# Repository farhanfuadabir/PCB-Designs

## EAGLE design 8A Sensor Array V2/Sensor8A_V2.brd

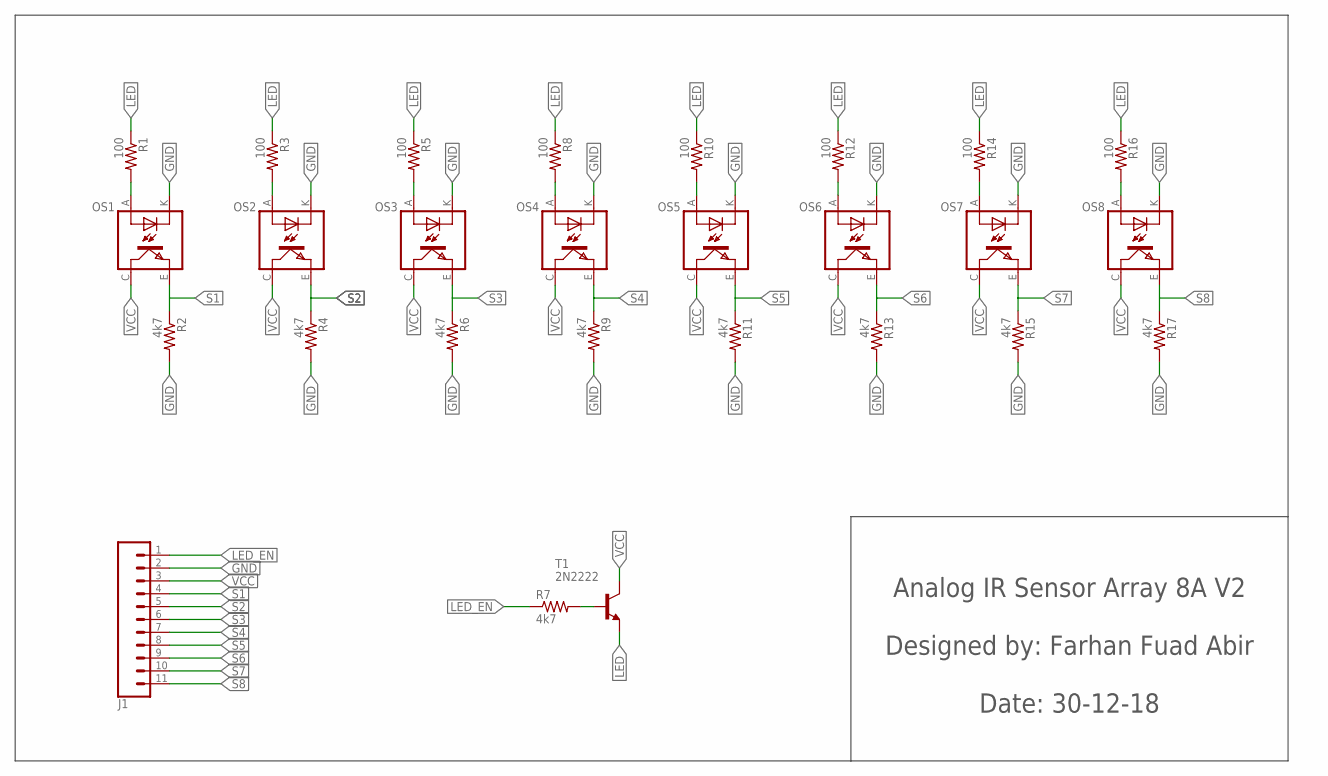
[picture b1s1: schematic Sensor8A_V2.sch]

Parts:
J1: CONN_11LONGPADS; 1X11_LONGPADS
OS1, OS2, OS3, OS4, OS5, OS6, OS7, OS8: TCRT5000
R1, R3, R5, R8, R10, R12, R14, R16: 100; 0204/7
R2, R4, R6, R7, R9, R11, R13, R15, R17: 4k7; 0204/7
T1: 2N2222; TO92-EBC-OVAL

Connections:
GND: J1.2, OS1.K (CATHODE), OS2.K (CATHODE), OS3.K (CATHODE), OS4.K (CATHODE), OS5.K (CATHODE), OS6.K (CATHODE), OS7.K (CATHODE), OS8.K (CATHODE), R2.2, R4.2, R6.2, R9.2, R11.2, R13.2, R15.2, R17.2
LED: R1.1, R3.1, R5.1, R8.1, R10.1, R12.1, R14.1, R16.1, T1.E
LED_EN: J1.1, R7.1
unnamed: OS1.A (ANODE), R1.2
unnamed: OS2.A (ANODE), R3.2
unnamed: OS3.A (ANODE), R5.2
unnamed: OS4.A (ANODE), R8.2
unnamed: OS5.A (ANODE), R10.2
unnamed: OS6.A (ANODE), R12.2
unnamed: OS7.A (ANODE), R14.2
unnamed: OS8.A (ANODE), R16.2
unnamed: R7.2, T1.B
S1: J1.4, OS1.E (EMITTER), R2.1
S2: J1.5, OS2.E (EMITTER), R4.1
S3: J1.6, OS3.E (EMITTER), R6.1
S4: J1.7, OS4.E (EMITTER), R9.1
S5: J1.8, OS5.E (EMITTER), R11.1
S6: J1.9, OS6.E (EMITTER), R13.1
S7: J1.10, OS7.E (EMITTER), R15.1
S8: J1.11, OS8.E (EMITTER), R17.1
VCC: J1.3, OS1.C (COLLECTOR), OS2.C (COLLECTOR), OS3.C (COLLECTOR), OS4.C (COLLECTOR), OS5.C (COLLECTOR), OS6.C (COLLECTOR), OS7.C (COLLECTOR), OS8.C (COLLECTOR), T1.C

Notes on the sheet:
Analog IR Sensor Array 8A V2 Designed by: Farhan Fuad Abir Date: 30-12-18

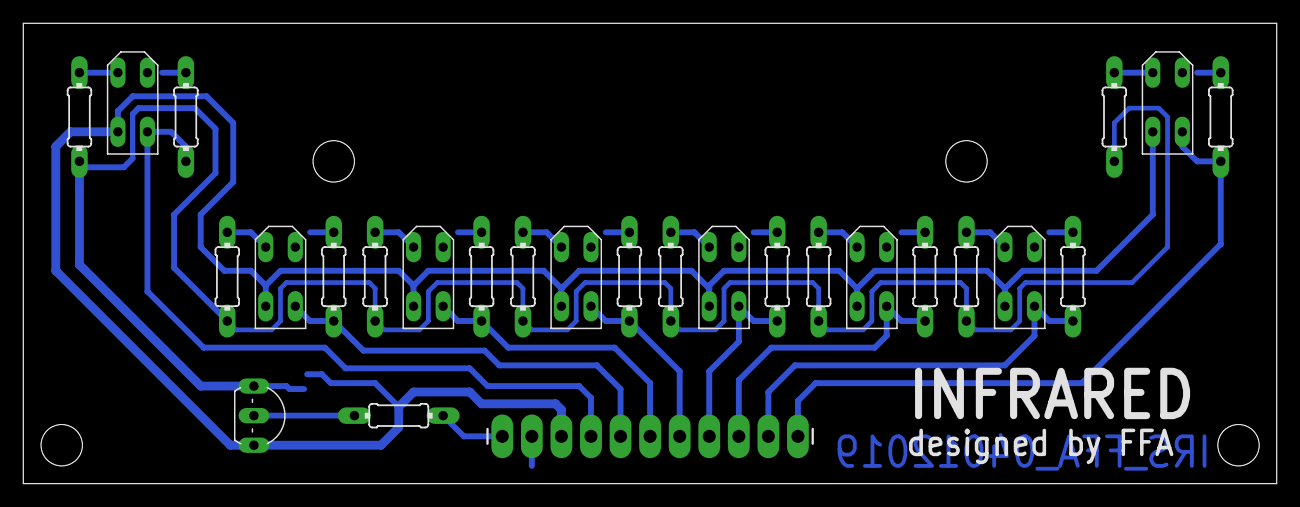
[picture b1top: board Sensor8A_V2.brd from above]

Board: 2 copper layers, 107.7 x 39.5 mm, 27 parts (0 on the bottom side), 21 nets.

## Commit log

2018-12-31 Added the Eagle Sensor array design files
2019-01-04 V1 updated and V2 added
2020-11-05 Create LICENSE

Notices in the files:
parts and their libraries:
SparkFun-Connectors: Licensing: Creative Commons ShareAlike 4.0 International - https://creativecommons.org/licenses/by-sa/4.0
